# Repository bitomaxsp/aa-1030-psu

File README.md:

# aa-1030-psu
Akai AA-1030 PSU

Model: Akai-1030 PSU A5-5309 4ED (TP-N88-S)

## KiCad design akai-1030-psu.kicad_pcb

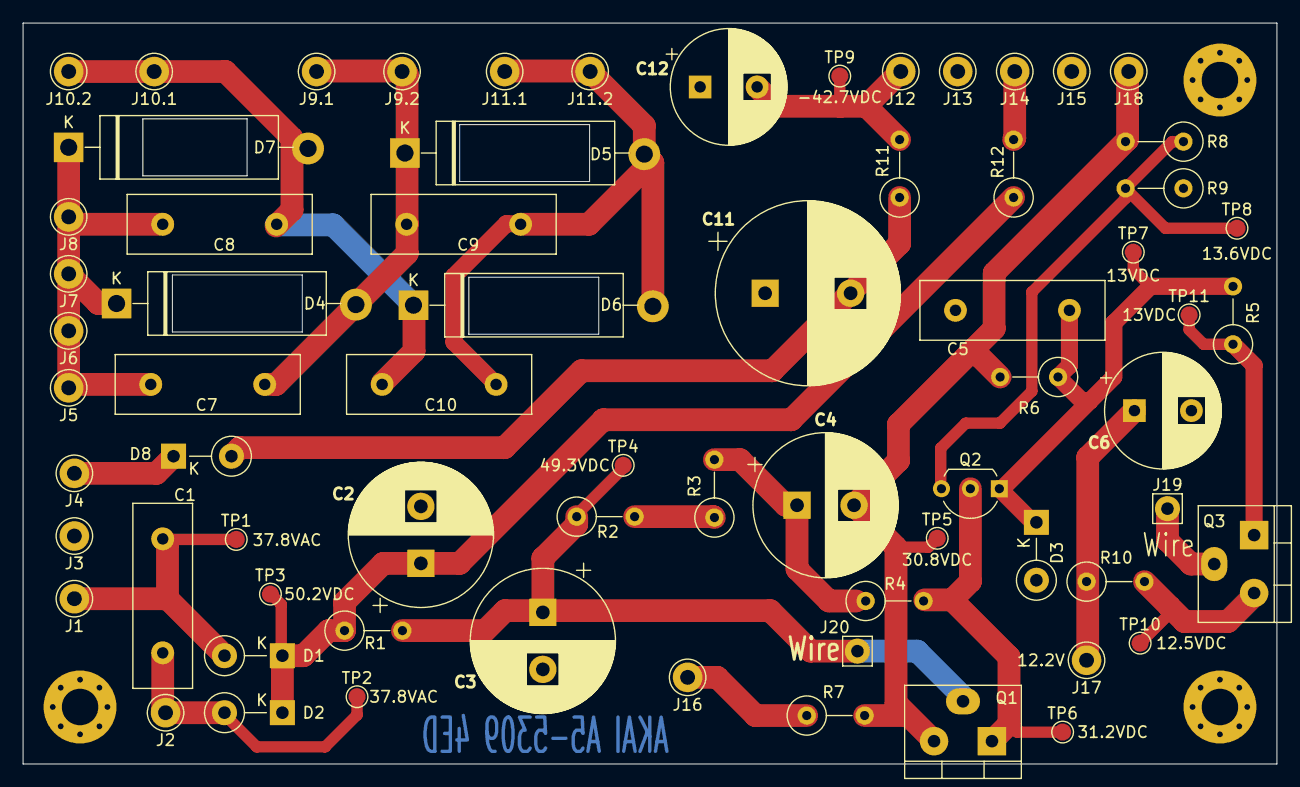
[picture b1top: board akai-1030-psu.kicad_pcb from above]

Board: 2 copper layers, 110.0 x 65.0 mm, 72 parts (0 on the bottom side), 24 nets.

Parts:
C1: 0.01uF; C_Disc_D16.0mm_W5.0mm_P10.00mm
C2: 330uF 63V; CP_Radial_D12.5mm_P5.00mm
C3: 330uF 50V; CP_Radial_D12.5mm_P5.00mm
C4: 470uF 10V; CP_Radial_D12.5mm_P5.00mm
C5: 0.01uF 50V; C_Disc_D16.0mm_W5.0mm_P10.00mm
C6: 220uF 16V; CP_Radial_D10.0mm_P5.00mm
C7, C8, C9, C10: 0.01uF 1.4kV; C_Disc_D16.0mm_W5.0mm_P10.00mm
C11: 1000uF 50V; CP_Radial_D16.0mm_P7.50mm
C12: 220uF 50V; CP_Radial_D10.0mm_P5.00mm
D1, D2, D8: 1N4003; D_DO-41_SOD81_P5.08mm_Vertical_KathodeUp
D3: WZ-130; D_DO-41_SOD81_P5.08mm_Vertical_KathodeUp
D4, D5, D6, D7: GI-618
H1, H2, H3: MountingHole_Pad; MountingHole_3.2mm_M3_Pad_Via
J1: #1; Pin_D1.3mm_L11.0mm
J2: #2; Pin_D1.3mm_L11.0mm
J3: #3; Pin_D1.3mm_L11.0mm
J4: #4; Pin_D1.3mm_L11.0mm
J5: #5; Pin_D1.3mm_L11.0mm
J6: #6; Pin_D1.3mm_L11.0mm
J7: #7; Pin_D1.3mm_L11.0mm
J8: #8; Pin_D1.3mm_L11.0mm
J9.1: #9.1; Pin_D1.3mm_L11.0mm
J9.2: #9.2; Pin_D1.3mm_L11.0mm
J10.1: #10.1; Pin_D1.3mm_L11.0mm
J10.2: #10.2; Pin_D1.3mm_L11.0mm
J11.1: #11.1; Pin_D1.3mm_L11.0mm
J11.2: #11.2; Pin_D1.3mm_L11.0mm
J12: #12; Pin_D1.3mm_L11.0mm
J13: #13; Pin_D1.3mm_L11.0mm
J14: #14; Pin_D1.3mm_L11.0mm
J15: #15; Pin_D1.3mm_L11.0mm
J16: 30.6VDC; Pin_D1.3mm_L11.0mm
J17: 12.2V; Pin_D1.3mm_L11.0mm
J18: #18; Pin_D1.3mm_L11.0mm
J19: #Q3-2; Pin_D1.1mm_L8.5mm_W2.5mm_FlatFork
J20: #Q1-2; Pin_D1.1mm_L8.5mm_W2.5mm_FlatFork
Q1, Q3: Q_NPN_BCE; TO-220-3-triangle
Q2: Q_NPN_ECB; TO-92L_Inline_Wide
R1: 10 1/2W; R_Axial_DIN0309_L9.0mm_D3.2mm_P5.08mm_Vertical
R2, R3, R4: 1k5; R_Axial_DIN0309_L9.0mm_D3.2mm_P5.08mm_Vertical
R5, R7: 10; R_Axial_DIN0309_L9.0mm_D3.2mm_P5.08mm_Vertical
R6: 2k2; R_Axial_DIN0309_L9.0mm_D3.2mm_P5.08mm_Vertical
R8: 27k; R_Axial_DIN0309_L9.0mm_D3.2mm_P5.08mm_Vertical
R9: 22k; R_Axial_DIN0309_L9.0mm_D3.2mm_P5.08mm_Vertical
R10: 4.7 1/2W; R_Axial_DIN0309_L9.0mm_D3.2mm_P5.08mm_Vertical
R11: 15 1/2W; R_Axial_DIN0309_L9.0mm_D3.2mm_P5.08mm_Vertical
R12: 3k3; R_Axial_DIN0309_L9.0mm_D3.2mm_P5.08mm_Vertical
TP1, TP2: 37.8VAC; TestPoint_Pad_D1.5mm
TP3: 50.2VDC; TestPoint_Pad_D1.5mm
TP4: 49.3VDC; TestPoint_Pad_D1.5mm
TP5: 30.8VDC; TestPoint_Pad_D1.5mm
TP6: 31.2VDC; TestPoint_Pad_D1.5mm
TP7, TP11: 13VDC; TestPoint_Pad_D1.5mm
TP8: 13.6VDC; TestPoint_Pad_D1.5mm
TP9: -42.7VDC; TestPoint_Pad_D1.5mm
TP10: 12.5VDC; TestPoint_Pad_D1.5mm

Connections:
GND: C2.2, C3.2, C5.2, C6.2, C11.1, C12.1, D3.2, H1.1, H2.1, H3.1, J3.1, J13.1, J15.1, R9.1
unnamed: C1.1, D1.2, J1.1, TP1.1
unnamed: C1.2, D2.2, J2.1, TP2.1
unnamed: C2.1, D1.1, D2.1, R1.1, R12.1, TP3.1
unnamed: C3.1, J20.1, Q1.2, R1.2, R2.1, TP4.1
unnamed: C4.1, R3.2, R4.1
unnamed: C4.2, J18.1, Q1.3, R6.2, R7.2, R8.2, TP5.1
unnamed: C5.1, D3.1, Q2.1, R5.2, R6.1, TP7.1
unnamed: C6.1, J17.1, R10.1
unnamed: C7.1, C8.1, D4.1, D7.1, J5.1, J6.1, J7.1, J8.1
unnamed: C7.2, C9.1, D4.2, D5.1, J9.1.1, J9.2.1
unnamed: C8.2, C10.1, D6.1, D7.2, J10.1.1, J10.2.1
unnamed: C9.2, C10.2, D5.2, D6.2, J11.1.1, J11.2.1
unnamed: C11.2, D8.2, R11.1
unnamed: C12.2, J12.1, R11.2, TP9.1
unnamed: D8.1, J4.1
unnamed: J14.1, R12.2
unnamed: J16.1, R7.1
unnamed: J19.1, Q3.2
unnamed: Q1.1, Q2.2, R4.2, TP6.1
unnamed: Q2.3, R8.1, R9.2, TP8.1
unnamed: Q3.1, R5.1, TP11.1
unnamed: Q3.3, R10.2, TP10.1
unnamed: R2.2, R3.1

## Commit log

2021-09-04 Add PSU 4ED
2021-09-04 Make revision B.
    - Give some space to J16 and J17 for easier mounting.
    - Move lower caps to the left
    - Move annotations
2021-11-27 Add model name
